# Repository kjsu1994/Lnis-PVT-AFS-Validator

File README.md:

# LNIS AFS End-to-End Validator

.NET 8 WPF에서 `LANS-AFS-SIM`과 `PocketSDR-AFS`를 별도 프로세스로 실행하여 AFS I/Q 생성, TCP 전송, 복호/PVT 처리 및 기준값 비교를 자동화한다.

## 1차 범위

```text
LANS-AFS-SIM -> INT8X2 I/Q -> TCP chunk/CRC32/SHA-256
             -> PocketSDR-AFS -> $LOG/$SB2/$POS -> 달 PVT 비교
```

실행에는 `LANS-AFS-SIM`과 `PocketSDR-AFS`만 사용한다. 범용 `PocketSDR`는 향후 GNSS 장비 Raw 입력과 지구 GNSS 기준 PVT Adapter를 구현할 때 참고한다. LNIS Codec, SF3/SF4 payload 삽입, BPv7/HDTN, SDR/RF와 실시간 스트리밍은 포함하지 않는다.

## 빌드

솔루션은 배포 가능한 WPF 본체 1개와 자동 테스트 프로젝트 1개로 구성된다. `Core`와 `Infrastructure`는 별도 프로젝트가 아닌 본체 내부 소스 폴더다.

```powershell
dotnet restore LnisAfsValidator.sln
dotnet build LnisAfsValidator.sln
dotnet test LnisAfsValidator.sln
dotnet run --project LnisAfsValidator.csproj
```

## WSL 준비

현재 확인 환경은 Ubuntu 24.04 WSL2이다. 애플리케이션은 패키지 설치나 저장소 복제를 자동 수행하지 않는다.

```bash
sudo apt update
sudo apt install build-essential git libusb-1.0-0-dev libfftw3-dev
cd /home/$USER
git clone https://github.com/osqzss/LANS-AFS-SIM.git
cd LANS-AFS-SIM && make

cd /home/$USER
git clone --recurse-submodules https://github.com/osqzss/PocketSDR-AFS.git
cd PocketSDR-AFS
git submodule update --init --recursive
cd lib/build && make && make install
cd ../../app/pocket_trk && make
```

기본 UI 경로는 `/home/imt` 기준 예시이므로 각 PC의 WSL 사용자 경로에 맞게 수정해야 한다. `O:` 드라이브 마운트에는 의존하지 않는다. WSL 산출물은 Windows의 `\\wsl.localhost\<배포판>\...` UNC를 통해 비동기로 읽고 쓴다.

## 사용 방법

공통으로 위치·시간 허용오차를 반드시 입력한다. `-b 2` 출력만 확인된 직접 호환 형식이므로 1차 UI는 `PocketSDR.INT8X2`, I/Q 2채널 형식을 고정 사용한다. 기준 시작 시각은 알마낙에서 결정된 생성기 stderr의 `Start time`을 사용한다.

### 로컬 시험

1. 역할을 `Local`로 선택한다.
2. 두 도구의 Native 또는 WSL 실행 경로와 작업 경로를 입력한다.
3. 월면 위치, 시험시간, 샘플률, 알마낙, PRN, 최소 위성 수와 허용오차를 입력한다.
4. `시험 시작`을 누른다. localhost에서도 실제 TCP 전송 경로를 사용한다.

### 두 PC 시험

1. 수신 PC에서 역할 `Receiver`, 사용할 포트와 PocketSDR-AFS 경로를 설정하고 먼저 시작한다.
2. OS 방화벽에서 해당 TCP 포트의 인바운드 연결을 허용한다.
3. 송신 PC에서 역할 `Sender`, 수신 PC 주소·동일 포트와 LANS-AFS-SIM 경로를 설정하고 시작한다.
4. 수신 PC는 무결성 ACK 후 복호/PVT를 수행하고 같은 연결로 최종 결과를 송신 PC에 반환한다.

## 판정과 결과

PASS에는 다음 근거가 모두 필요하다.

- 전송 byte count, chunk 순서, IEEE CRC32와 전체 SHA-256 일치
- 설정한 최소 위성 수 이상의 `SIGNAL FOUND`
- 최소 위성 수 이상의 `$SB2` 성공: AFS frame sync와 SB2 LDPC/CRC 성공의 간접 근거
- `$POS`와 마지막 필드의 실제 관측 위성 수
- 최종 `$POS` 위치·시간 오차가 사용자가 입력한 허용치 이내
- PocketSDR-AFS 정상 종료

명확한 필수 조건 위반은 Fail, 로그 형식 미지원이나 기준값 파싱 불가 등 근거 부족은 Inconclusive이다. `$POS`의 끝에서 두 번째 위성 수는 현재 AFS 소스에서 상수 `5`이므로 판정에 사용하지 않는다. `$SB3/$SB4`와 frame error는 기록하지만 1차 필수 조건은 아니다.

결과는 `%LOCALAPPDATA%\LnisAfsValidator\Runs` 아래에 manifest, JSON 결과, 생성기/수신기 원본 로그와 함께 저장한다. PASS면 대용량 I/Q를 삭제하고 Fail/Inconclusive이면 원본 분석을 위해 보관한다. 마지막 UI 설정은 `%LOCALAPPDATA%\LnisAfsValidator\settings.json`에 저장한다.

## TCP 프로토콜 v1

- magic/version: ASCII `LAFSIQ01`
- 최대 64 KiB 길이 제한 JSON manifest
- chunk: big-endian index, payload length, IEEE CRC32, payload
- 기본 chunk 1 MiB, 허용 범위 4 KiB~16 MiB, 기본 최대 파일 32 GiB
- 수신 경로는 원격 파일명을 사용하지 않고 시험 GUID로 생성
- SHA-256 확인 전에는 `.partial`, 성공 후에만 `.iq`로 원자적 변경

## 확장 지점

- `IIqDataSource`: 현재 LANS-AFS-SIM, 향후 GNSS 장비 Raw 및 PocketSDR 기준 PVT Adapter
- `IArtifactTransport`: 현재 TCP, 향후 BPv7/HDTN
- `IAfsReceiverAdapter`: 현재 PocketSDR-AFS, 향후 다른 AFS 수신기
- `IVerdictEvaluator`: 향후 LNIS message 및 SF3/SF4 비교

GNSS 장비 Raw 형식이 확인되기 전에는 이를 `Unknown` 산출물로 취급하고 성공으로 판정하지 않아야 한다. LNIS payload와 BPv7 bundle을 AFS SF3/SF4에 넣는 규격이 확인된 뒤 별도 Adapter로 구현한다.

## 현재 검증 제약

- .NET 솔루션 빌드와 자동 테스트는 수행 가능하다.
- 현재 PC의 WSL에는 필수 개발 패키지와 빌드된 오픈소스 실행 파일이 없어 실제 90초 AFS E2E는 아직 실행하지 못했다.
- 저장소에 AFS 실제 실행 로그 fixture가 없어 파서 테스트는 실제 소스에서 확인한 로그 형식을 사용한다. WSL 빌드 후 생성한 원본 로그로 fixture를 교체·보강해야 한다.
- `O:`가 WSL `/mnt/o`에 자동 마운트되지 않는 환경을 기준으로 UNC staging을 구현했다.

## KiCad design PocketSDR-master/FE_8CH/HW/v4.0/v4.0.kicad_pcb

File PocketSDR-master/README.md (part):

# **Pocket SDR - An Open-Source GNSS SDR,<br> ver. 0.19**

<div style="text-align: right;">
<strong>2026-07-24</strong>
</div>

---

## **Overview**

**Pocket SDR** is an open-source Global Navigation Satellite System (GNSS) receiver based
on software-defined radio (SDR) technology. It consists of RF frontend devices named
**Pocket SDR FE**, utilities for these devices, and GNSS SDR applications (APs) written
in Python, C, and C++. It supports almost all signals for **GPS**, **GLONASS**, **Galileo**,
**QZSS**, **BeiDou**, **NavIC**, and **SBAS**.

The Pocket SDR FE device includes 2, 4, or 8 RF frontend channels, supporting the
GNSS L1 band (1525 - 1610 MHz) or L2/L5/L6 bands (1160 - 1290 MHz). For these signal bands, refer to [**GNSS Signal Bands**](https://github.com/tomojitakasu/PocketSDR/blob/master/doc/signal_bands.pdf). Each RF channel
of the Pocket SDR FE device provides IF (intermediate-frequency) bandwidth of up to 36 MHz. The ADC sampling rate can be configured up to 32 Msps (FE 2CH) or 48 Msps (FE 4CH and FE 8CH).

Pocket SDR also includes utility programs to configure the Pocket SDR FE devices,
capture, and dump digitized IF data.
Additionally, Pocket SDR provides GNSS SDR APs to display the PSD (power spectrum density) of captured IF data, search for GNSS signals, track these signals, decode navigation data, and generate PVT (position, velocity, and time) solutions.
These utilities and APs are compatible with **Windows**, **Linux**, **Raspberry Pi OS**, **macOS**, and other environments.

The supported GNSS signals by Pocket SDR are as follows. For details on these signals and Pocket SDR signal IDs, refer to
[**GNSS Signals**](https://github.com/tomojitakasu/PocketSDR/blob/master/doc/signal_IDs.pdf).

* **GPS**: L1C/A, L1C-D, L1C-P, L2C-M, L5-I, L5-Q
* **GLONASS**: L1C/A (L1OF), L2C/A (L2OF), L1OCd, L1OCp, L2OCp, L3OCd, L3OCp
* **Galileo**: E1-B, E1-C, E5a-I, E5a-Q, E5b-I, E5b-Q, E5AltBOC (E5abQ), E6-B, E6-C
* **QZSS**: L1C/A, L1C/B, L1C-D, L1C-P, L1S, L2C-M, L5-I, L5-Q, L5S-I, L5S-Q, L6D, L6E
* **BeiDou**: B1I, B1C-D, B1C-P, B2a-D, B2a-P, B2I, B2b-I, B3I
* **NavIC**: L1-SPS-D, L1-SPS-P, L5-SPS
* **SBAS**: L1C/A, L5-I, L5-Q

These utilities and APs are written in Python, C, and C++ in a compact and modular way,
making them easy to modify for adding custom algorithms.

In addition to the Pocket SDR FE devices, Pocket SDR supports third-party
SDR hardware (**USRP**, **LimeSDR**, **bladRF**, **PlutoSDR**, **RTL-SDR**, and so on) via 
[**SoapySDR**](https://github.com/pothosware/SoapySDR/wiki).
See [**SoapySDR Device Notes**](https://github.com/tomojitakasu/PocketSDR/blob/master/doc/notes_soapy_dev.md) for verified devices,
installation notes, and device-specific caveats.

<p align="center">
  
  <b>Pocket SDR FE 2CH (v.2.0 and v.2.3), FE 4CH</b>
</p>

<p align="center">
  
  <b>Pocket SDR FE 8CH (2-RF-inputs and 8-RF-inputs)</b>
</p>

<p align="center">
  
  <b>GUI-based Real-Time GNSS SDR Receiver AP</b>
</p>

--------------------------------------------------------------------------------
<div class="pagebreak"></div>

## **Documents**

- Pocket SDR C Library API Reference
(https://github.com/tomojitakasu/PocketSDR/tree/master/doc/api_ref.pdf)

- Pocket SDR Command Reference
(https://github.com/tomojitakasu/PocketSDR/tree/master/doc/command_ref.pdf)

- Pocket SDR GNSS SDR Algorithm Description
(https://github.com/tomojitakasu/PocketSDR/tree/master/doc/algo_desc.pdf)

- Pocket SDR GNSS SDR アルゴリズム解説
(https://github.com/tomojitakasu/PocketSDR/tree/master/doc/algo_desc_jp.pdf)

- T.Takasu, An Open Source GNSS SDR: Development and Application, IPNTJ Next GNSS
Technology WG, February 21, 2022
(https://gpspp.sakura.ne.jp/paper2005/IPNTJ_NEXTWG_202202.pdf)

- T.Takasu, Development of QZSS L6 Receiver without Pilot Signal by using SDR,
IPNTJ Annual Conference, June 10, 2022
(https://gpspp.sakura.ne.jp/paper2005/IPNTJ_20220610.pdf)

- T.Takasu, Pocket SDR: Design, Implementation and Applications, A seminar for
GNSS Software Defined Receivers, Nov 19, 2024
(https://gpspp.sakura.ne.jp/paper2005/pocketsdr_seminar_202411_revA.pdf)

--------------------------------------------------------------------------------
<div class="pagebreak"></div>

## **Directory Structure and Contents**
```
PocketSDR
├── bin         # Pocket SDR APs binary programs
├── app         # Pocket SDR APs source programs
│   ├── pocket_conf  # Pocket SDR FE device configurator
│   ├── pocket_dump  # Dump digital IF data of Pocket SDR FE device
│   ├── pocket_scan  # Scan and list USB devices
│   ├── pocket_acq   # GNSS signal acquisition
│   ├── pocket_trk   # GNSS signal tracking and PVT generation
│   ├── pocket_snap  # Snapshot Positioning
│   ├── pocket_calib # Antenna array attitude / per-CH bias calibration
│   ├── convbin      # RINEX converter supporting Pocket SDR
│   └── str2str      # Stream converter (RTKLIB-derived)
├── src         # Pocket SDR library source programs
├── python      # Pocket SDR Python scripts (incl. pocket_sdr.py GUI)
├── lib         # Libraries for APs and Python scripts
│   ├── win32        # Built libraries for Windows (UCRT64)
│   ├── macos        # Built libraries for macOS
│   ├── linux        # Built libraries for Linux or Raspberry Pi OS
│   ├── build        # Makefiles to build libraries (UCRT64 / Linux / macOS)
│   ├── cyusb        # Cypress EZ-USB API (CyAPI.a) and includes
│   ├── RTKLIB       # RTKLIB source programs based on 2.4.3 b34
│   ├── pocketfft    # PocketFFT (header-only FFT, used internally)
│   └── SoapySDR     # SoapySDR headers + import lib for SDR device support
├── conf        # Configuration files for Pocket SDR FE
├── FE_2CH      # Pocket SDR FE 2CH H/W and F/W
├── FE_4CH      # Pocket SDR FE 4CH H/W and F/W
├── FE_8CH      # Pocket SDR FE 8CH H/W and F/W (3-bit RF samples)
├── driver      # Driver installation instruction for Pocket SDR FE
├── doc         # Documents (incl. api_ref.md, command_ref.md)
├── image       # Image files for documents
├── sample      # Sample digital IF data captured by Pocket SDR FE
└── test        # Test codes, scripts and data
    ├── python       # Python scripts for tests
    ├── script       # Shell scripts for tests
    ├── src          # source programs for tests
    └── utest        # makefile for unit tests

```
--------------------------------------------------------------------------------
<div class="pagebreak"></div>

## **Installation for Windows**

* Download and extract PocketSDR.zip or clone the git repository [**here**](https://github.com/tomojitakasu/PocketSDR) to an appropriate directory <install_dir>.
to an appropriate directory <install_dir>.
```
> unzip PocketSDR.zip
or
> git clone https://github.com/tomojitakasu/PocketSDR
```
* Install USB device driver for Pocket SDR FE according to [**driver/readme.txt**](https://github.com/tomojitakasu/PocketSDR/blob/master/driver/readme.txt)
.
* Install [**Python**](https://www.python.org/) with checking "Add python.exe to PATH".
* Install additional python packages as follows.
```
> pip install numpy scipy matplotlib
```
* (Optional) To use SoapySDR-supported devices (LimeSDR, HackRF, RTL-SDR,
  bladeRF, etc.), install [**radioconda**](https://github.com/ryanvolz/radioconda)
  and add `<radioconda_install_dir>\Library\bin` to PATH. See
  [SoapySDR Device Notes](https://github.com/tomojitakasu/PocketSDR/blob/master/doc/notes_soapy_dev.md#windows) for per-device
  packages, Zadig driver setup, and bladeRF version caveats.
* Add the Pocket SDR binary programs path (<install_dir>\PocketSDR\bin) to 
  the command search path (Path) of Windows environment variables.
* Add the Pocket SDR Python scripts path (<install_dir>\PocketSDR\python) to 
  the command search path (Path) of Windows environment variables.

--------------------------------------------------------------------------------

## **To rebuild binary programs for Windows**
* If you want to rebuild the binary utilities, APs, or shared libraries for the python APs
for Windows, you need [**MSYS2**](https://www.msys2.org/) with the **UCRT64** environment.
The UCRT64 toolchain links against the same C runtime (`ucrtbase.dll`) as
[**radioconda**](https://github.com/ryanvolz/radioconda)'s SoapySDR DLLs, which
gives stable high-rate streaming with SDR hardware (e.g., LimeSDR at 64 Msps).
The legacy **MINGW64** environment also builds, but suffers significant
performance loss with SoapySDR devices due to msvcrt/UCRT mixing.

* Open the **MSYS2 UCRT64** shell and install the development tools and the
  Python stack used by the python APs:
```
$ pacman -Syy
$ pacman -S git make
$ pacman -S mingw-w64-ucrt-x86_64-gcc
$ pacman -S mingw-w64-ucrt-x86_64-binutils
$ pacman -S mingw-w64-ucrt-x86_64-python
$ pacman -S mingw-w64-ucrt-x86_64-python-numpy
$ pacman -S mingw-w64-ucrt-x86_64-python-scipy
$ pacman -S mingw-w64-ucrt-x86_64-python-matplotlib
```
* If you intend to use SoapySDR-supported devices, install radioconda first.
  The default radioconda location used by the Makefiles is
  `/c/Users/<user>/radioconda/Library`. If installed elsewhere, override
  with `SOAPY_ROOT` on the make command line. See
  [SoapySDR Device Notes](https://github.com/tomojitakasu/PocketSDR/blob/master/doc/notes_soapy_dev.md#windows-build-notes)
  for details.

* If SoapySDR device support is not required, build `libsdr`, `pocket_trk`,
  and `pocket_dump` with `USE_SOAPY=0`. Pocket SDR FE USB devices and
  IF-file based processing still work; only SoapySDR device input is
  disabled. If you are rebuilding an existing tree, run `make clean` first.
```
$ cd <install_dir>/lib/build
$ make clean && make USE_SOAPY=0 && make install
$ cd <install_dir>/app/pocket_trk
$ make clean && make USE_SOAPY=0 && make install
$ cd <install_dir>/app/pocket_dump
$ make clean && make USE_SOAPY=0 && make install
```

* Move to the library build directory and build libraries.
```
$ cd <install_dir>/lib/build
$ make
$ make install
```
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
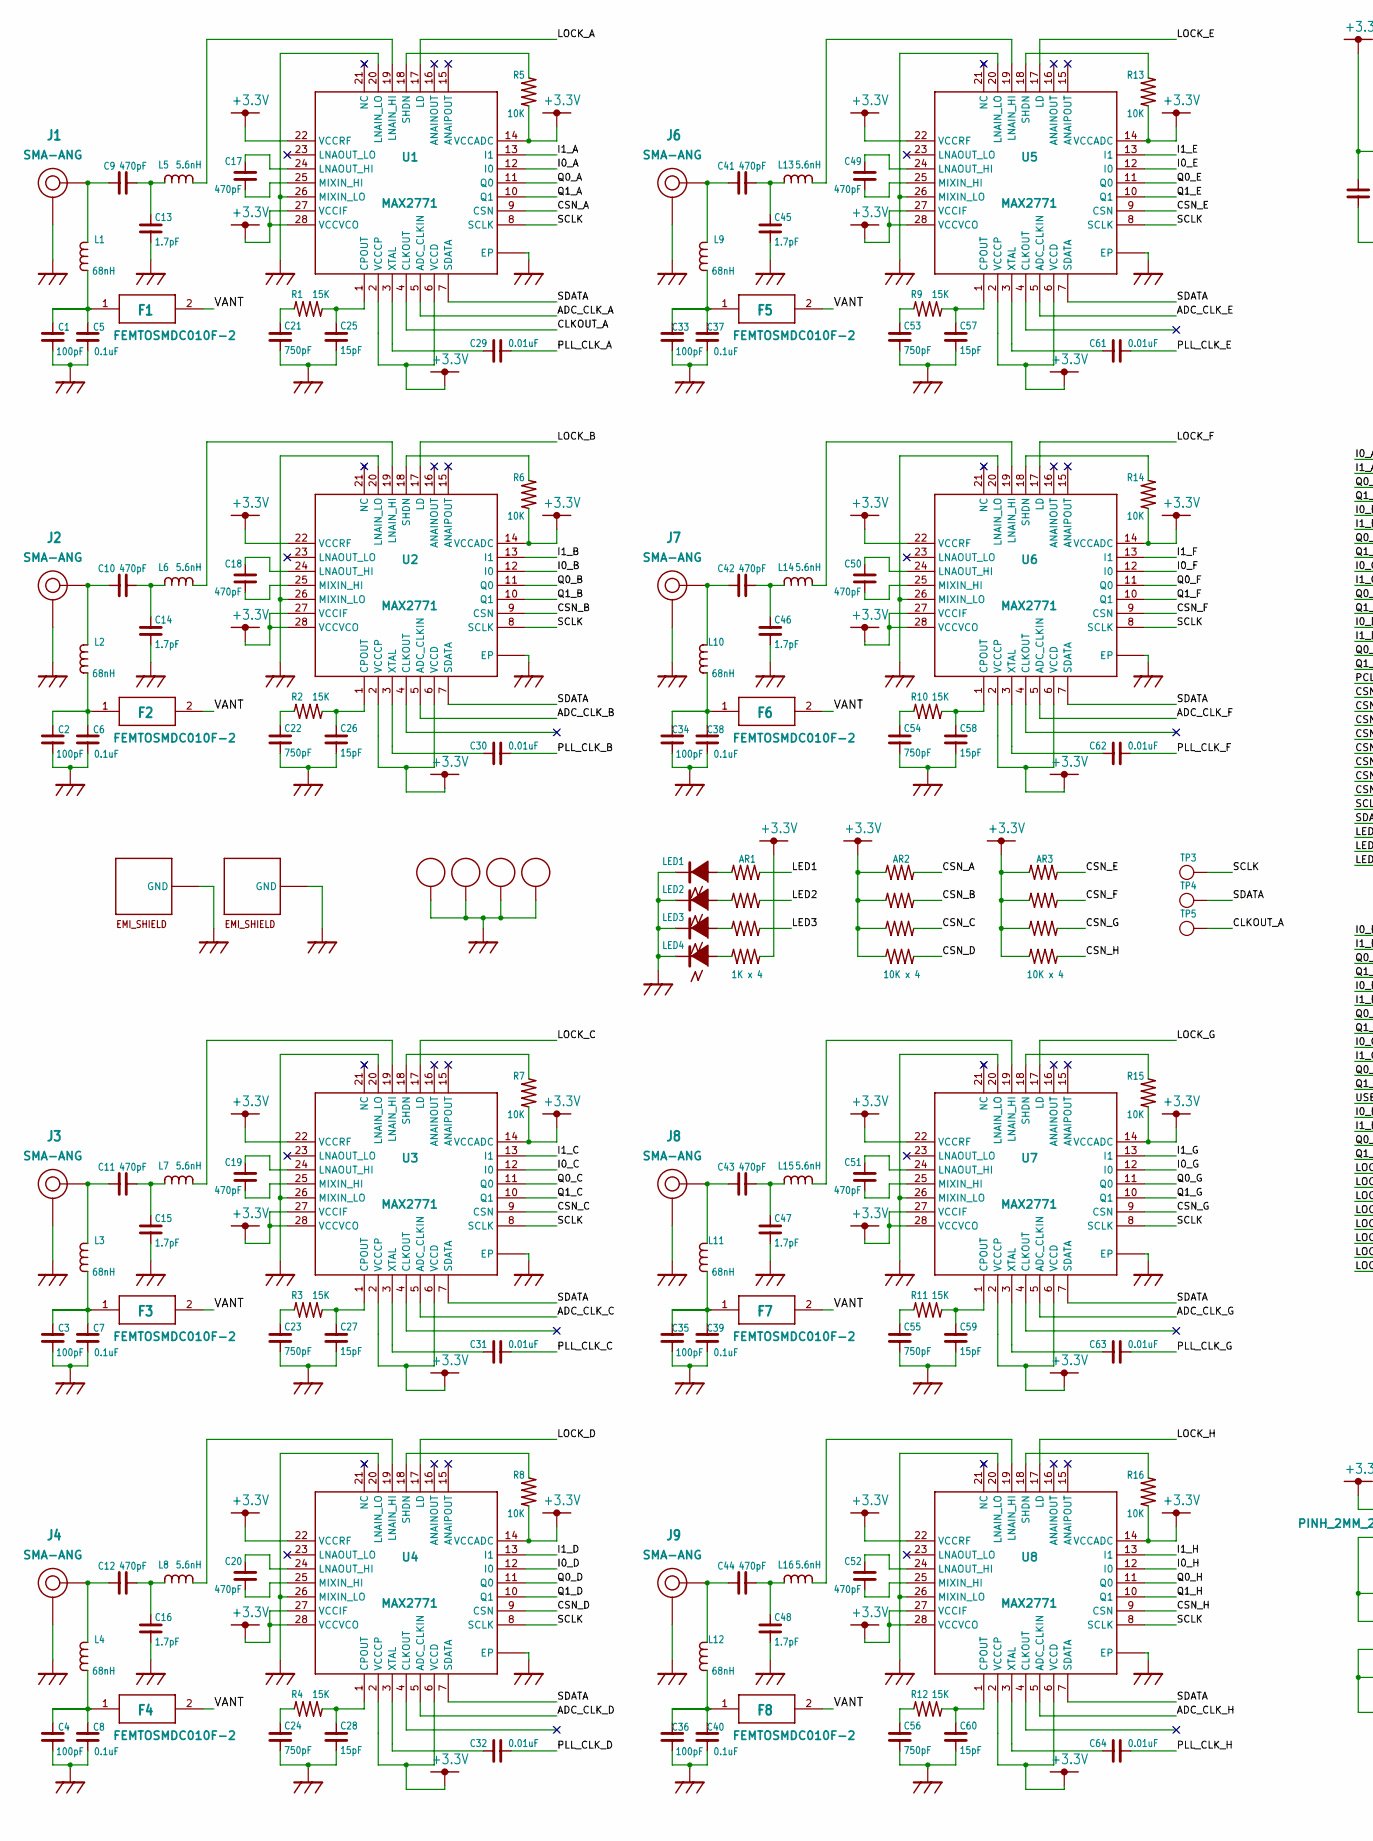
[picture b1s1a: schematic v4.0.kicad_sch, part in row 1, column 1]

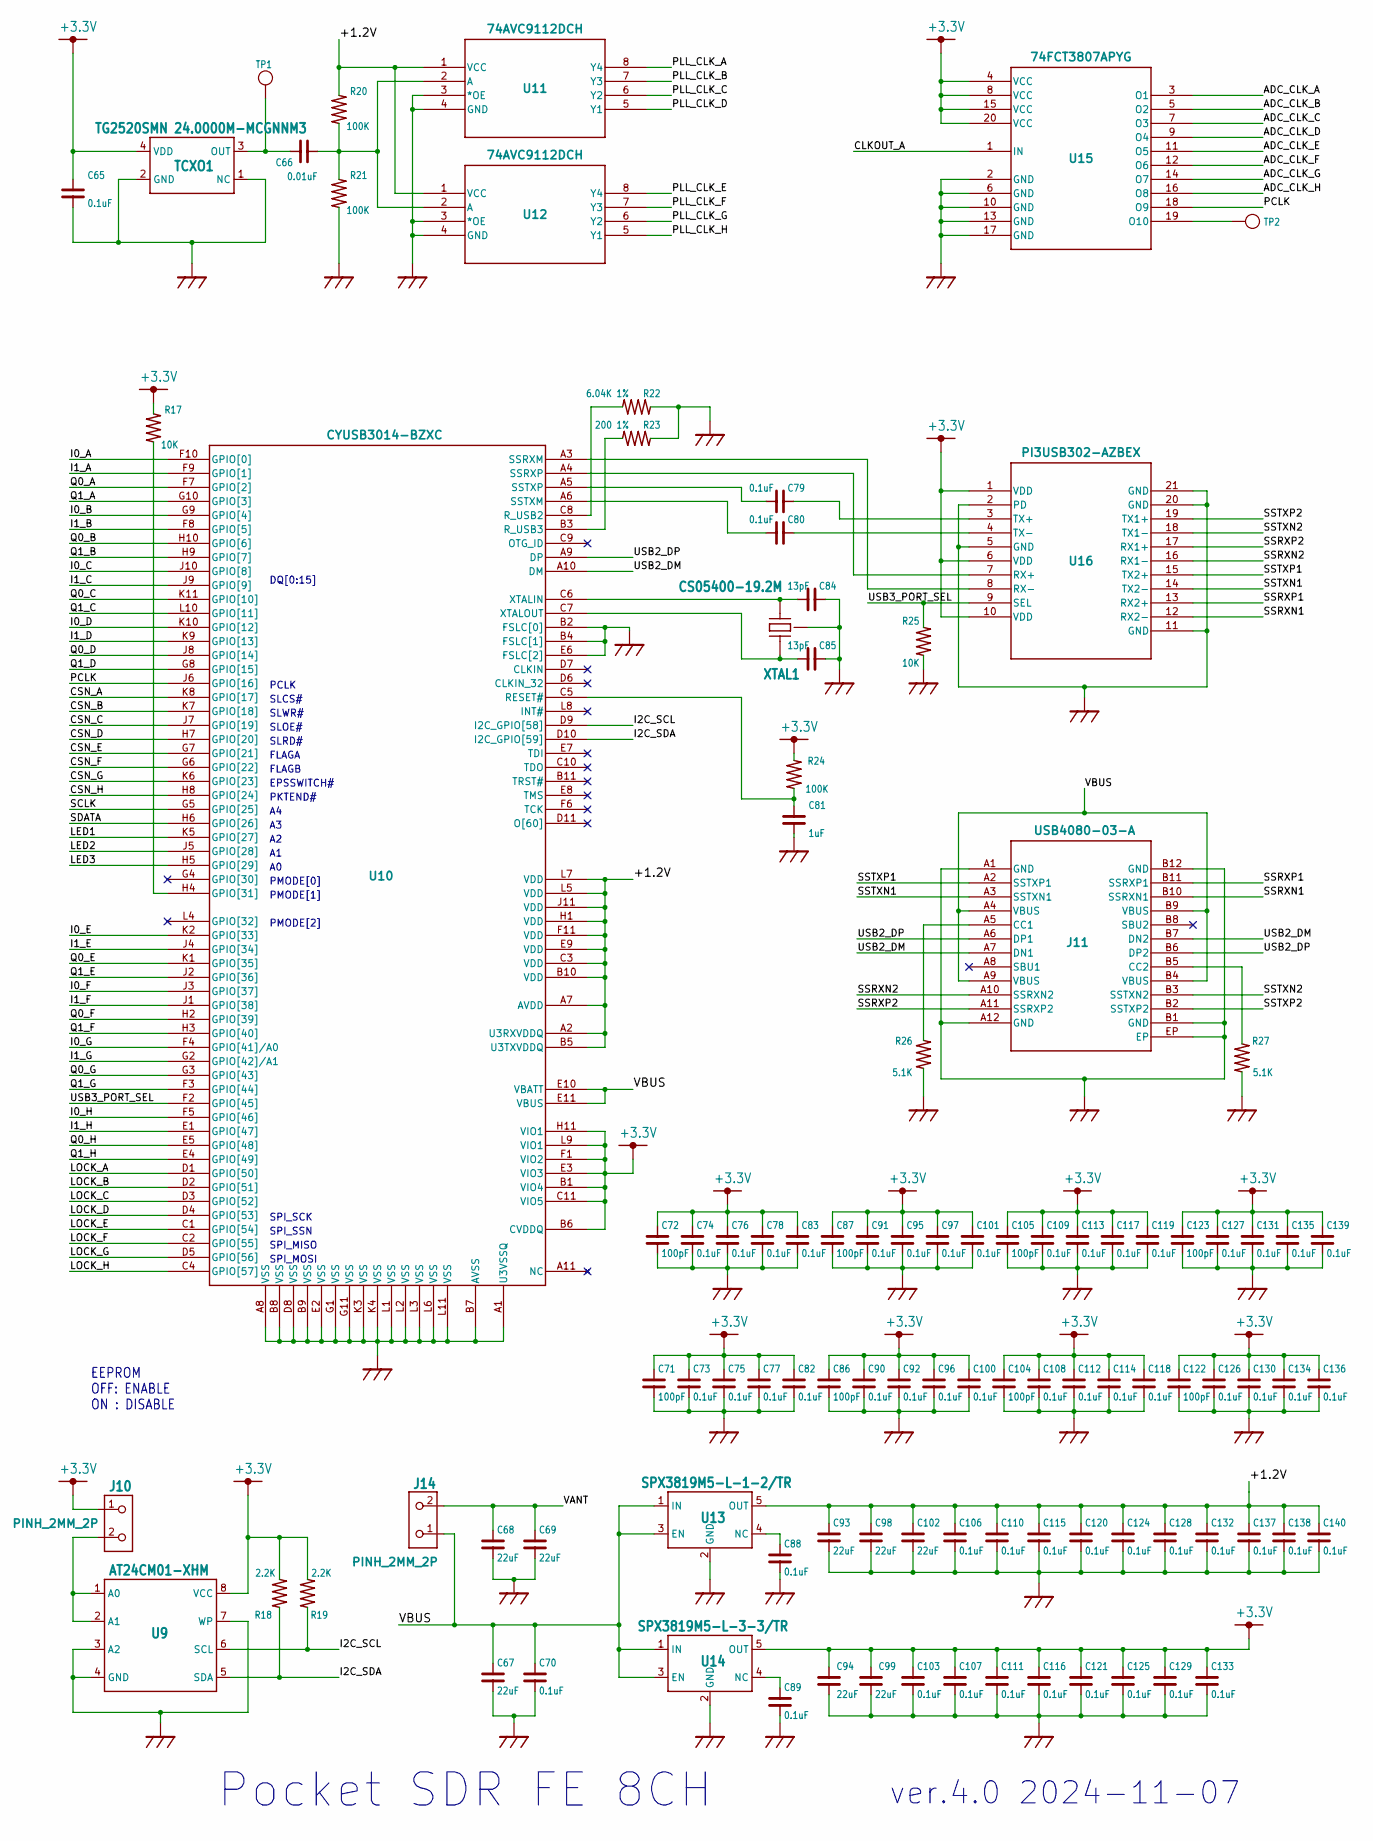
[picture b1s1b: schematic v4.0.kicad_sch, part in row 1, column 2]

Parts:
AR1: 1K x 4; EXB28V
AR2, AR3: 10K x 4; EXB28V
C1, C2, C3, C4, C33, C34, C35, C36, C71, C72, C86, C87, C104, C105, C122, C123: 100pF; C1005
C5, C6, C7, C8, C37, C38, C39, C40, C65, C70, C73, C74, C75, C76, C77, C78, C79, C80, C82, C83, C88, C89, C90, C91, C92, C95, C96, C97, C100, C101, C103, C106, C107, C108, C109, C110, C111, C112, C113, C114, C115, C116, C117, C118, C119, C120, C121, C124, C125, C126, C127, C128, C129, C130, C131, C132, C133, C134, C135, C136, C137, C138, C139, C140: 0.1uF; C1005
C9, C10, C11, C12, C17, C18, C19, C20, C41, C42, C43, C44, C49, C50, C51, C52: 470pF; C1005
C13, C14, C15, C16, C45, C46, C47, C48: 1.7pF; C1005
C21, C22, C23, C24, C53, C54, C55, C56: 750pF; C1005
C25, C26, C27, C28, C57, C58, C59, C60: 15pF; C1005
C29, C30, C31, C32, C61, C62, C63, C64, C66: 0.01uF; C1005
C67, C68, C69, C93, C94, C98, C99, C102: 22uF; C1608
C81: 1uF; C1005
C84, C85: 13pF; C1005
F1, F2, F3, F4, F5, F6, F7, F8: FEMTOSMDC010F-2; C1608
J1, J2, J3, J4, J6, J7, J8, J9: SMA-ANG
J10, J14: PINH_2MM_2P; PINH-2MM-2P
J11: USB4080-03-A; USB4080-03-A_GCT
J12, J13: MS448-10F
L1, L2, L3, L4, L9, L10, L11, L12: 68nH; C1608
L5, L6, L7, L8, L13, L14, L15, L16: 5.6nH; C1005
LED1, LED2, LED3, LED4: LED1608; LED_1608
PAD1, PAD2, PAD3, PAD4: CPAD_3.2MM
R1, R2, R3, R4, R9, R10, R11, R12: 15K; C1005
R5, R6, R7, R8, R13, R14, R15, R16, R17, R25: 10K; C1005
R18, R19: 2.2K; C1005
R20, R21, R24: 100K; C1005
R22: 6.04K 1%; C1005
R23: 200 1%; C1005
R26, R27: 5.1K; C1005
TCXO1: TG2520SMN 24.0000M-MCGNNM3; TCXO
TP1, TP2, TP3, TP4, TP5: TP0.5
U1, U2, U3, U4, U5, U6, U7, U8: MAX2771; TQFN28
U9: AT24CM01-XHM; TSSOP_8P
U10: CYUSB3014-BZXC; BGA-121
U11, U12: 74AVC9112DCH; VSSOP8_SOT765-1_NEX
U13: SPX3819M5-L-1-2/TR; SOT23
U14: SPX3819M5-L-3-3/TR; SOT23
U15: 74FCT3807APYG; SSOP20
U16: PI3USB302-AZBEX; 20TQFN-ZB_PI3USB302-A_DIO
XTAL1: CS05400-19.2M; XTAL_SMD

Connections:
+3.3V: AR1.8, AR2.1, AR2.3, AR2.5, AR2.7, AR3.1, AR3.3, AR3.5, AR3.7, C65.1, C71.1, C72.1, C73.1, C74.1, C75.1, C76.1, C77.1, C78.1, C82.1, C83.1, C86.1, C87.1, C90.1, C91.1, C92.1, C94.1, C95.1, C96.1, C97.1, C99.1, C100.1, C101.1, C103.1, C104.1, C105.1, C107.1, C108.1, C109.1, C111.1, C112.1, C113.1, C114.1, C116.1, C117.1, C118.1, C119.1, C121.1, C122.1, C123.1, C125.1, C126.1, C127.1, C129.1, C130.1, C131.1, C133.1, C134.1, C135.1, C136.1, C139.1, J10.1, R5.1, R6.1, R7.1, R8.1, R13.1, R14.1, R15.1, R16.1, R17.1, R18.2, R19.2, R24.2, TCXO1.4 (VDD), U1.2 (VCCCP), U1.6 (VCCD), U1.14 (VCCADC), U1.22 (VCCRF), U1.27 (VCCIF), U1.28 (VCCVCO), U2.2 (VCCCP), U2.6 (VCCD), U2.14 (VCCADC), U2.22 (VCCRF), U2.27 (VCCIF), U2.28 (VCCVCO), U3.2 (VCCCP), U3.6 (VCCD), U3.14 (VCCADC), U3.22 (VCCRF), U3.27 (VCCIF), U3.28 (VCCVCO), U4.2 (VCCCP), U4.6 (VCCD), U4.14 (VCCADC), U4.22 (VCCRF), U4.27 (VCCIF), U4.28 (VCCVCO), U5.2 (VCCCP), U5.6 (VCCD), U5.14 (VCCADC), U5.22 (VCCRF), U5.27 (VCCIF), U5.28 (VCCVCO), U6.2 (VCCCP), U6.6 (VCCD), U6.14 (VCCADC), U6.22 (VCCRF), U6.27 (VCCIF), U6.28 (VCCVCO), U7.2 (VCCCP), U7.6 (VCCD), U7.14 (VCCADC), U7.22 (VCCRF), U7.27 (VCCIF), U7.28 (VCCVCO), U8.2 (VCCCP), U8.6 (VCCD), U8.14 (VCCADC), U8.22 (VCCRF), U8.27 (VCCIF), U8.28 (VCCVCO), U9.8 (VCC), U10.B1 (VIO4), U10.B6 (CVDDQ), U10.C11 (VIO5), U10.E3 (VIO3), U10.F1 (VIO2), U10.H11 (VIO1), U10.L9 (VIO1), U14.5 (OUT), U15.4 (VCC), U15.8 (VCC), U15.15 (VCC), U15.20 (VCC), U16.1 (VDD), U16.6 (VDD), U16.10 (VDD)
/+1.2V: C93.1, C98.1, C102.1, C106.1, C110.1, C115.1, C120.1, C124.1, C128.1, C132.1, C137.1, C138.1, C140.1, R20.1, U10.A2 (U3RXVDDQ), U10.A7 (AVDD), U10.B5 (U3TXVDDQ), U10.B10 (VDD), U10.C3 (VDD), U10.E9 (VDD), U10.F11 (VDD), U10.H1 (VDD), U10.J11 (VDD), U10.L5 (VDD), U10.L7 (VDD), U11.1 (VCC), U12.1 (VCC), U13.5 (OUT)
/ADC_CLK_A: U1.5 (ADC_CLKIN), U15.3 (O1)
/ADC_CLK_B: U2.5 (ADC_CLKIN), U15.5 (O2)
/ADC_CLK_C: U3.5 (ADC_CLKIN), U15.7 (O3)
/ADC_CLK_D: U4.5 (ADC_CLKIN), U15.9 (O4)
/ADC_CLK_E: U5.5 (ADC_CLKIN), U15.11 (O5)
/ADC_CLK_F: U6.5 (ADC_CLKIN), U15.12 (O6)
/ADC_CLK_G: U7.5 (ADC_CLKIN), U15.14 (O7)
/ADC_CLK_H: U8.5 (ADC_CLKIN), U15.16 (O8)
/CLKOUT_A: TP5.1, U1.4 (CLKOUT), U15.1 (IN)
/CSN_A: AR2.2, U1.9 (CSN), U10.K8 (GPIO[17])
/CSN_B: AR2.4, U2.9 (CSN), U10.K7 (GPIO[18])
/CSN_C: AR2.6, U3.9 (CSN), U10.J7 (GPIO[19])
/CSN_D: AR2.8, U4.9 (CSN), U10.H7 (GPIO[20])
/CSN_E: AR3.2, U5.9 (CSN), U10.G7 (GPIO[21])
/CSN_F: AR3.4, U6.9 (CSN), U10.G6 (GPIO[22])
/CSN_G: AR3.6, U7.9 (CSN), U10.K6 (GPIO[23])
/CSN_H: AR3.8, U8.9 (CSN), U10.H8 (GPIO[24])
/I0_A: U1.12 (I0), U10.F10 (GPIO[0])
/I0_B: U2.12 (I0), U10.G9 (GPIO[4])
/I0_C: U3.12 (I0), U10.J10 (GPIO[8])
/I0_D: U4.12 (I0), U10.K10 (GPIO[12])
/I0_E: U5.12 (I0), U10.K2 (GPIO[33])
/I0_F: U6.12 (I0), U10.J3 (GPIO[37])
/I0_G: U7.12 (I0), U10.F4 (GPIO[41]/A0)
/I0_H: U8.12 (I0), U10.F5 (GPIO[46])
/I1_A: U1.13 (I1), U10.F9 (GPIO[1])
/I1_B: U2.13 (I1), U10.F8 (GPIO[5])
/I1_C: U3.13 (I1), U10.J9 (GPIO[9])
/I1_D: U4.13 (I1), U10.K9 (GPIO[13])
/I1_E: U5.13 (I1), U10.J4 (GPIO[34])
/I1_F: U6.13 (I1), U10.J1 (GPIO[38])
/I1_G: U7.13 (I1), U10.G2 (GPIO[42]/A1)
/I1_H: U8.13 (I1), U10.E1 (GPIO[47])
/I2C_SCL: R19.1, U9.6 (SCL), U10.D9 (I2C_GPIO[58])
/I2C_SDA: R18.1, U9.5 (SDA), U10.D10 (I2C_GPIO[59])
/LED1: AR1.2, U10.K5 (GPIO[27])
/LED2: AR1.4, U10.J5 (GPIO[28])
/LED3: AR1.6, U10.H5 (GPIO[29])
/LOCK_A: U1.17 (LD), U10.D1 (GPIO[50])
/LOCK_B: U2.17 (LD), U10.D2 (GPIO[51])
/LOCK_C: U3.17 (LD), U10.D3 (GPIO[52])
/LOCK_D: U4.17 (LD), U10.D4 (GPIO[53])
/LOCK_E: U5.17 (LD), U10.C1 (GPIO[54])
/LOCK_F: U6.17 (LD), U10.C2 (GPIO[55])
/LOCK_G: U7.17 (LD), U10.D5 (GPIO[56])
/LOCK_H: U8.17 (LD), U10.C4 (GPIO[57])
/PCLK: U10.J6 (GPIO[16]), U15.18 (O9)
/PLL_CLK_A: C29.1, U11.8 (Y4)
/PLL_CLK_B: C30.1, U11.7 (Y3)
/PLL_CLK_C: C31.1, U11.6 (Y2)
/PLL_CLK_D: C32.1, U11.5 (Y1)
/PLL_CLK_E: C61.1, U12.8 (Y4)
/PLL_CLK_F: C62.1, U12.7 (Y3)
/PLL_CLK_G: C63.1, U12.6 (Y2)
/PLL_CLK_H: C64.1, U12.5 (Y1)
/Q0_A: U1.11 (Q0), U10.F7 (GPIO[2])
/Q0_B: U2.11 (Q0), U10.H10 (GPIO[6])
/Q0_C: U3.11 (Q0), U10.K11 (GPIO[10])
/Q0_D: U4.11 (Q0), U10.J8 (GPIO[14])
/Q0_E: U5.11 (Q0), U10.K1 (GPIO[35])
/Q0_F: U6.11 (Q0), U10.H2 (GPIO[39])
/Q0_G: U7.11 (Q0), U10.G3 (GPIO[43])
/Q0_H: U8.11 (Q0), U10.E5 (GPIO[48])
/Q1_A: U1.10 (Q1), U10.G10 (GPIO[3])
/Q1_B: U2.10 (Q1), U10.H9 (GPIO[7])
/Q1_C: U3.10 (Q1), U10.L10 (GPIO[11])
/Q1_D: U4.10 (Q1), U10.G8 (GPIO[15])
/Q1_E: U5.10 (Q1), U10.J2 (GPIO[36])
/Q1_F: U6.10 (Q1), U10.H3 (GPIO[40])
/Q1_G: U7.10 (Q1), U10.F3 (GPIO[44])
/Q1_H: U8.10 (Q1), U10.E4 (GPIO[49])
/SCLK: TP3.1, U1.8 (SCLK), U2.8 (SCLK), U3.8 (SCLK), U4.8 (SCLK), U5.8 (SCLK), U6.8 (SCLK), U7.8 (SCLK), U8.8 (SCLK), U10.G5 (GPIO[25])
/SDATA: TP4.1, U1.7 (SDATA), U2.7 (SDATA), U3.7 (SDATA), U4.7 (SDATA), U5.7 (SDATA), U6.7 (SDATA), U7.7 (SDATA), U8.7 (SDATA), U10.H6 (GPIO[26])
/SSRXN1: J11.B10 (SSRXN1), U16.12 (RX2-)
/SSRXN2: J11.A10 (SSRXN2), U16.16 (RX1-)
/SSRXP1: J11.B11 (SSRXP1), U16.13 (RX2+)
/SSRXP2: J11.A11 (SSRXP2), U16.17 (RX1+)
/SSTXN1: J11.A3 (SSTXN1), U16.14 (TX2-)
/SSTXN2: J11.B3 (SSTXN2), U16.18 (TX1-)
/SSTXP1: J11.A2 (SSTXP1), U16.15 (TX2+)
/SSTXP2: J11.B2 (SSTXP2), U16.19 (TX1+)
/USB2_DM: J11.A7 (DN1), J11.B7 (DN2), U10.A10 (DM)
/USB2_DP: J11.A6 (DP1), J11.B6 (DP2), U10.A9 (DP)
/USB3_PORT_SEL: R25.2, U10.F2 (GPIO[45]), U16.9 (SEL)
/VANT: C68.1, C69.1, F1.2, F2.2, F3.2, F4.2, F5.2, F6.2, F7.2, F8.2, J14.2
/VBUS: C67.1, C70.1, J11.A4 (VBUS), J11.A9 (VBUS), J11.B4 (VBUS), J11.B9 (VBUS), J14.1, U10.E10 (VBATT), U10.E11 (VBUS), U13.1 (IN), U13.3 (EN), U14.1 (IN), U14.3 (EN)
GND: C1.1, C2.1, C3.1, C4.1, C5.1, C6.1, C7.1, C8.1, C13.1, C14.1, C15.1, C16.1, C21.2, C22.2, C23.2, C24.2, C25.2, C26.2, C27.2, C28.2, C33.1, C34.1, C35.1, C36.1, C37.1, C38.1, C39.1, C40.1, C45.1, C46.1, C47.1, C48.1, C53.2, C54.2, C55.2, C56.2, C57.2, C58.2, C59.2, C60.2, C65.2, C67.2, C68.2, C69.2, C70.2, C71.2, C72.2, C73.2, C74.2, C75.2, C76.2, C77.2, C78.2, C81.2, C82.2, C83.2, C84.1, C85.1, C86.2, C87.2, C88.2, C89.2, C90.2, C91.2, C92.2, C93.2, C94.2, C95.2, C96.2, C97.2, C98.2, C99.2, C100.2, C101.2, C102.2, C103.2, C104.2, C105.2, C106.2, C107.2, C108.2, C109.2, C110.2, C111.2, C112.2, C113.2, C114.2, C115.2, C116.2, C117.2, C118.2, C119.2, C120.2, C121.2, C122.2, C123.2, C124.2, C125.2, C126.2, C127.2, C128.2, C129.2, C130.2, C131.2, C132.2, C133.2, C134.2, C135.2, C136.2, C137.2, C138.2, C139.2, C140.2, J1.P2 (GND), J1.P3 (GND), J1.P4 (GND), J1.P5 (GND), J2.P2 (GND), J2.P3 (GND), J2.P4 (GND), J2.P5 (GND), J3.P2 (GND), J3.P3 (GND), J3.P4 (GND), J3.P5 (GND), J4.P2 (GND), J4.P3 (GND), J4.P4 (GND), J4.P5 (GND), J6.P2 (GND), J6.P3 (GND), J6.P4 (GND), J6.P5 (GND), J7.P2 (GND), J7.P3 (GND), J7.P4 (GND), J7.P5 (GND), J8.P2 (GND), J8.P3 (GND), J8.P4 (GND), J8.P5 (GND), J9.P2 (GND), J9.P3 (GND), J9.P4 (GND), J9.P5 (GND), J11.A1 (GND), J11.A12 (GND), J11.B1 (GND), J11.B12 (GND), J11.EP, J12.P (GND), J13.P (GND), LED1.2, LED2.2, LED3.2, LED4.2, PAD1.EP, PAD2.EP, PAD3.EP, PAD4.EP, R21.2, R22.1, R23.1, R25.1, R26.1, R27.1, TCXO1.1 (NC), TCXO1.2 (GND), U1.20 (LNAIN_LO), U1.26 (MIXIN_LO), U1.C1 (EP), U1.C2 (EP), U1.C3 (EP), U1.C4 (EP), U1.EP, U1.V1 (EP), U1.V2 (EP), U1.V3 (EP), U1.V4 (EP), U1.V5 (EP), U1.V6 (EP), U1.V7 (EP), U1.V8 (EP), U1.V9 (EP), U2.20 (LNAIN_LO), U2.26 (MIXIN_LO), U2.C1 (EP), U2.C2 (EP), U2.C3 (EP), U2.C4 (EP), U2.EP, U2.V1 (EP), U2.V2 (EP), U2.V3 (EP), U2.V4 (EP), U2.V5 (EP), U2.V6 (EP), U2.V7 (EP), U2.V8 (EP), U2.V9 (EP), U3.20 (LNAIN_LO), U3.26 (MIXIN_LO), U3.C1 (EP), U3.C2 (EP), U3.C3 (EP), U3.C4 (EP), U3.EP, U3.V1 (EP), U3.V2 (EP), U3.V3 (EP), U3.V4 (EP), U3.V5 (EP), U3.V6 (EP), U3.V7 (EP), U3.V8 (EP), U3.V9 (EP), U4.20 (LNAIN_LO), U4.26 (MIXIN_LO), U4.C1 (EP), U4.C2 (EP), U4.C3 (EP), U4.C4 (EP), U4.EP, U4.V1 (EP), U4.V2 (EP), U4.V3 (EP), U4.V4 (EP), U4.V5 (EP), U4.V6 (EP), U4.V7 (EP), U4.V8 (EP), U4.V9 (EP), U5.20 (LNAIN_LO), U5.26 (MIXIN_LO), U5.C1 (EP), U5.C2 (EP), U5.C3 (EP), U5.C4 (EP), U5.EP, U5.V1 (EP), U5.V2 (EP), U5.V3 (EP), U5.V4 (EP), U5.V5 (EP), U5.V6 (EP), U5.V7 (EP), U5.V8 (EP), U5.V9 (EP), U6.20 (LNAIN_LO), U6.26 (MIXIN_LO), U6.C1 (EP), U6.C2 (EP), U6.C3 (EP), U6.C4 (EP), U6.EP, U6.V1 (EP), U6.V2 (EP), U6.V3 (EP), U6.V4 (EP), U6.V5 (EP), U6.V6 (EP), U6.V7 (EP), U6.V8 (EP), U6.V9 (EP), U7.20 (LNAIN_LO), U7.26 (MIXIN_LO), U7.C1 (EP), U7.C2 (EP), U7.C3 (EP), U7.C4 (EP), U7.EP, U7.V1 (EP), U7.V2 (EP), U7.V3 (EP), U7.V4 (EP), U7.V5 (EP), U7.V6 (EP), U7.V7 (EP), U7.V8 (EP), U7.V9 (EP), U8.20 (LNAIN_LO), U8.26 (MIXIN_LO), U8.C1 (EP), U8.C2 (EP), U8.C3 (EP), U8.C4 (EP), U8.EP, U8.V1 (EP), U8.V2 (EP), U8.V3 (EP), U8.V4 (EP), U8.V5 (EP), U8.V6 (EP), U8.V7 (EP), U8.V8 (EP), U8.V9 (EP), U9.3 (A2), U9.4 (GND), U9.7 (WP), U10.A1 (U3VSSQ), U10.A8 (VSS), U10.B2 (FSLC[0]), U10.B4 (FSLC[1]), U10.B7 (AVSS), U10.B8 (VSS), U10.B9 (VSS), U10.D8 (VSS), U10.E2 (VSS), U10.E6 (FSLC[2]), U10.G1 (VSS), U10.G11 (VSS), U10.K3 (VSS), U10.K4 (VSS), U10.L1 (VSS), U10.L2 (VSS), U10.L3 (VSS), U10.L6 (VSS), U10.L11 (VSS), U11.3 (*OE), U11.4 (GND), U12.3 (*OE), U12.4 (GND), U13.2 (GND), U14.2 (GND), U15.2 (GND), U15.6 (GND), U15.10 (GND), U15.13 (GND), U15.17 (GND), U16.2 (PD), U16.5 (GND), U16.11 (GND), U16.20 (GND), U16.21 (GND), XTAL1.P2 (GND), XTAL1.P4 (GND)
unnamed: AR1.1, LED1.1 (+)
unnamed: AR1.3, LED2.1 (+)
unnamed: AR1.5, LED3.1 (+)
unnamed: AR1.7, LED4.1 (+)
unnamed: C1.2, C5.2, F1.1, L1.1
unnamed: C2.2, C6.2, F2.1, L2.1
unnamed: C3.2, C7.2, F3.1, L3.1
unnamed: C4.2, C8.2, F4.1, L4.1
unnamed: C33.2, C37.2, F5.1, L9.1
unnamed: C34.2, C38.2, F6.1, L10.1
unnamed: C35.2, C39.2, F7.1, L11.1
unnamed: C36.2, C40.2, F8.1, L12.1
unnamed: C9.1, J1.P1 (RF), L1.2
unnamed: C10.1, J2.P1 (RF), L2.2
unnamed: C11.1, J3.P1 (RF), L3.2
unnamed: C12.1, J4.P1 (RF), L4.2
unnamed: C41.1, J6.P1 (RF), L9.2
unnamed: C42.1, J7.P1 (RF), L10.2
unnamed: C43.1, J8.P1 (RF), L11.2
unnamed: C44.1, J9.P1 (RF), L12.2
unnamed: J10.2, U9.1 (A0), U9.2 (A1)
unnamed: J11.A5 (CC1), R26.2
unnamed: J11.B5 (CC2), R27.2
unnamed: C9.2, C13.2, L5.1
unnamed: L5.2, U1.19 (LNAIN_HI)
unnamed: C10.2, C14.2, L6.1
unnamed: L6.2, U2.19 (LNAIN_HI)
unnamed: C11.2, C15.2, L7.1
unnamed: L7.2, U3.19 (LNAIN_HI)
unnamed: C12.2, C16.2, L8.1
unnamed: L8.2, U4.19 (LNAIN_HI)
unnamed: C41.2, C45.2, L13.1
unnamed: L13.2, U5.19 (LNAIN_HI)
unnamed: C42.2, C46.2, L14.1
unnamed: L14.2, U6.19 (LNAIN_HI)
unnamed: C43.2, C47.2, L15.1
unnamed: L15.2, U7.19 (LNAIN_HI)
unnamed: C44.2, C48.2, L16.1
unnamed: L16.2, U8.19 (LNAIN_HI)
unnamed: C21.1, R1.1
unnamed: C25.1, R1.2, U1.1 (CPOUT)
unnamed: C22.1, R2.1
unnamed: C26.1, R2.2, U2.1 (CPOUT)
unnamed: C23.1, R3.1
unnamed: C27.1, R3.2, U3.1 (CPOUT)
unnamed: C24.1, R4.1
unnamed: C28.1, R4.2, U4.1 (CPOUT)
unnamed: R5.2, U1.18 (SHDN)
unnamed: R6.2, U2.18 (SHDN)
unnamed: R7.2, U3.18 (SHDN)
unnamed: R8.2, U4.18 (SHDN)
unnamed: C53.1, R9.1
unnamed: C57.1, R9.2, U5.1 (CPOUT)
unnamed: C54.1, R10.1
unnamed: C58.1, R10.2, U6.1 (CPOUT)
unnamed: C55.1, R11.1
unnamed: C59.1, R11.2, U7.1 (CPOUT)
unnamed: C56.1, R12.1
unnamed: C60.1, R12.2, U8.1 (CPOUT)
unnamed: R13.2, U5.18 (SHDN)
unnamed: R14.2, U6.18 (SHDN)
unnamed: R15.2, U7.18 (SHDN)
unnamed: R16.2, U8.18 (SHDN)
unnamed: R17.2, U10.H4 (GPIO[31])
unnamed: C66.2, R20.2, R21.1, U11.2 (A), U12.2 (A)
unnamed: R22.2, U10.C8 (R_USB2)
unnamed: R23.2, U10.B3 (R_USB3)
unnamed: C81.1, R24.1, U10.C5 (RESET#)
unnamed: C66.1, TCXO1.3 (OUT), TP1.1
unnamed: C17.1, U1.24 (LNAOUT_HI)
unnamed: C17.2, U1.25 (MIXIN_HI)
unnamed: C29.2, U1.3 (XTAL)
unnamed: C18.1, U2.24 (LNAOUT_HI)
unnamed: C18.2, U2.25 (MIXIN_HI)
unnamed: C30.2, U2.3 (XTAL)
unnamed: C19.1, U3.24 (LNAOUT_HI)
unnamed: C19.2, U3.25 (MIXIN_HI)
unnamed: C31.2, U3.3 (XTAL)
unnamed: C20.1, U4.24 (LNAOUT_HI)
unnamed: C20.2, U4.25 (MIXIN_HI)
unnamed: C32.2, U4.3 (XTAL)
unnamed: C49.1, U5.24 (LNAOUT_HI)
unnamed: C49.2, U5.25 (MIXIN_HI)
unnamed: C61.2, U5.3 (XTAL)
unnamed: C50.1, U6.24 (LNAOUT_HI)
unnamed: C50.2, U6.25 (MIXIN_HI)
unnamed: C62.2, U6.3 (XTAL)
unnamed: C51.1, U7.24 (LNAOUT_HI)
unnamed: C51.2, U7.25 (MIXIN_HI)
unnamed: C63.2, U7.3 (XTAL)
unnamed: C52.1, U8.24 (LNAOUT_HI)
unnamed: C52.2, U8.25 (MIXIN_HI)
unnamed: C64.2, U8.3 (XTAL)
unnamed: U10.A3 (SSRXM), U16.8 (RX-)
unnamed: U10.A4 (SSRXP), U16.7 (RX+)
unnamed: C80.2, U10.A6 (SSTXM)
unnamed: C79.2, U10.A5 (SSTXP)
unnamed: C84.2, U10.C6 (XTALIN), XTAL1.P1 (XTAL1)
unnamed: C85.2, U10.C7 (XTALOUT), XTAL1.P3 (XTAL2)
unnamed: C88.1, U13.4 (NC)
unnamed: C89.1, U14.4 (NC)
unnamed: TP2.1, U15.19 (O10)
unnamed: C79.1, U16.3 (TX+)
unnamed: C80.1, U16.4 (TX-)

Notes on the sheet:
PCLK
EPSSWITCH#
SPI_SSN
PMODE[1]
DQ[0:15]
Pocket SDR FE 8CH
PMODE[0]
EEPROM OFF: ENABLE ON : DISABLE
SPI_SCK
SPI_MOSI
SLRD#
SLOE#
SLCS#
PMODE[2]
SLWR#
PKTEND#
ver.4.0 2024-11-07
SPI_MISO
FLAGA
FLAGB

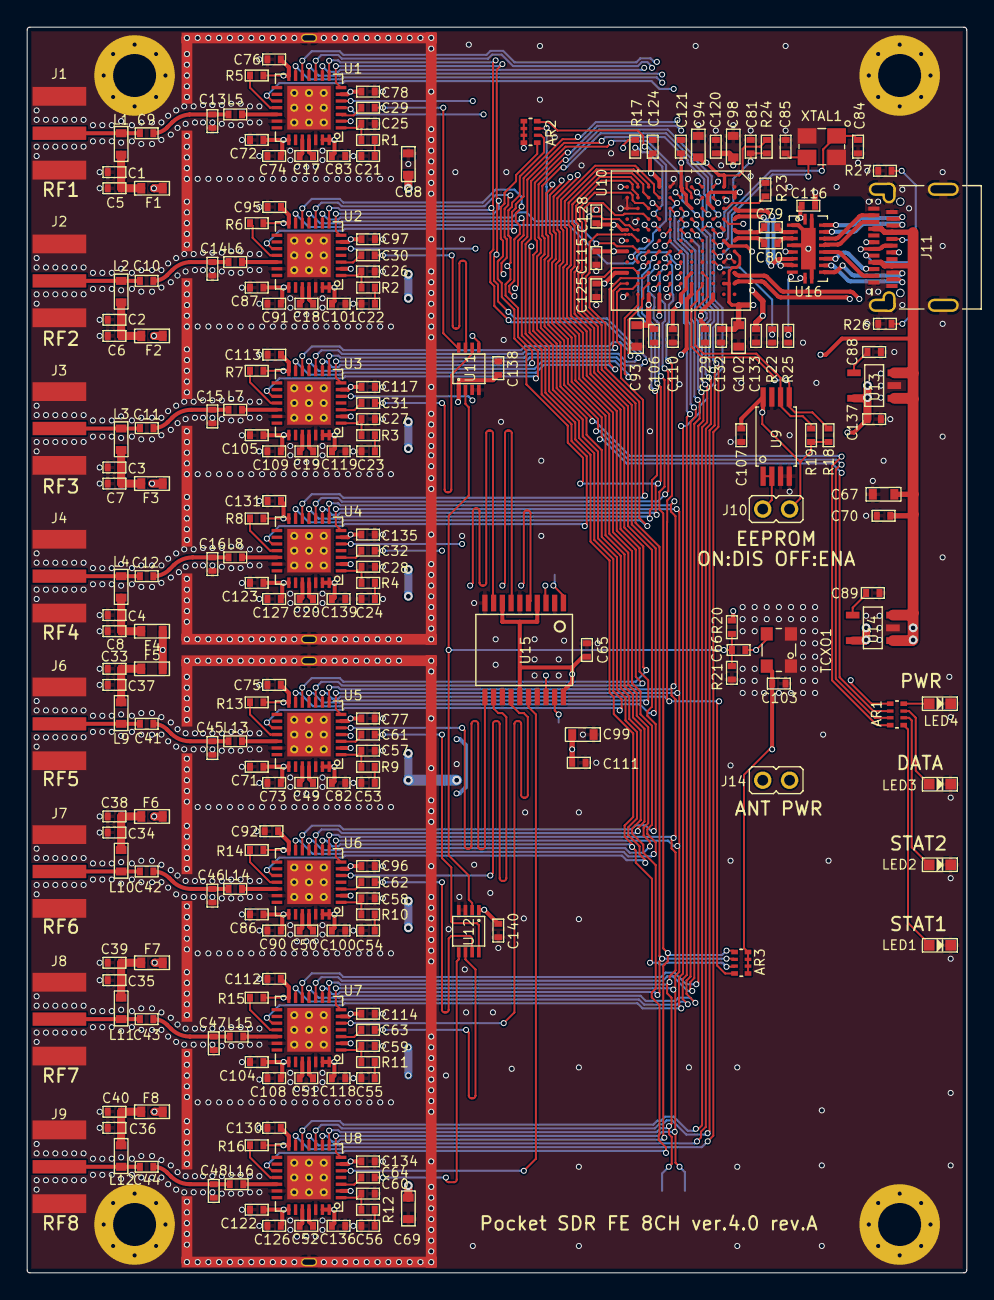
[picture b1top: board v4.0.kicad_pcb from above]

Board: 4 copper layers, 70.0 x 92.8 mm, 238 parts (0 on the bottom side), 193 nets.

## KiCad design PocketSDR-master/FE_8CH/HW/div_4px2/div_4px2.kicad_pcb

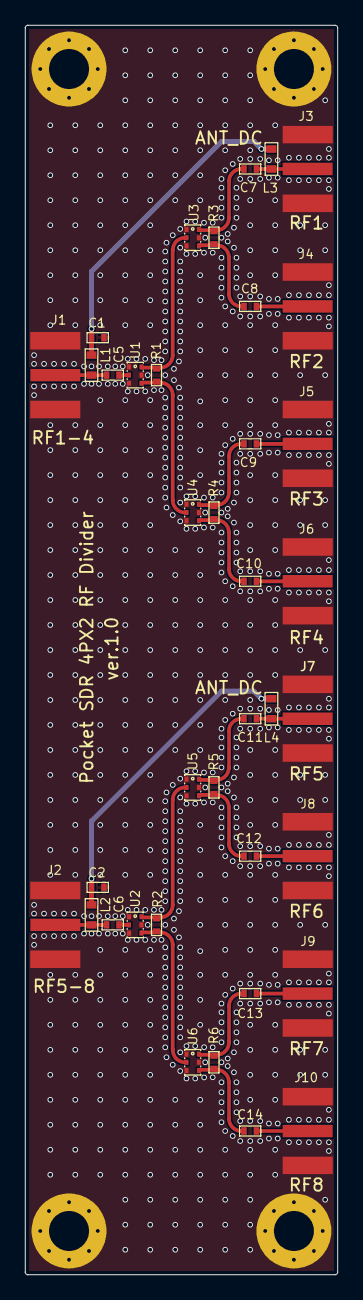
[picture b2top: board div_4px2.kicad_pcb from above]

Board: 4 copper layers, 25.0 x 100.0 mm, 42 parts (0 on the bottom side), 27 nets.

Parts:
C1, C2: 0.1uF; C1005
C5, C6, C7, C8, C9, C10, C11, C12, C13, C14: 100pF; C1005
J1, J2, J3, J4, J5, J6, J7, J8, J9, J10: SMA-ANG
L1, L2, L3, L4: 68nH; C1608
PAD1, PAD2, PAD3, PAD4: CPAD_3.2MM
R1, R2, R3, R4, R5, R6: 100; C1005
U1, U2, U3, U4, U5, U6: PD0922J5050S2HF; RF_DIV

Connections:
/ANT_DC1: C1.2, L1.1, L3.1
/ANT_DC2: C2.2, L2.1, L4.1
GND: C1.1, C2.1, J1.P2 (GND), J1.P3 (GND), J1.P4 (GND), J1.P5 (GND), J2.P2 (GND), J2.P3 (GND), J2.P4 (GND), J2.P5 (GND), J3.P2 (GND), J3.P3 (GND), J3.P4 (GND), J3.P5 (GND), J4.P2 (GND), J4.P3 (GND), J4.P4 (GND), J4.P5 (GND), J5.P2 (GND), J5.P3 (GND), J5.P4 (GND), J5.P5 (GND), J6.P2 (GND), J6.P3 (GND), J6.P4 (GND), J6.P5 (GND), J7.P2 (GND), J7.P3 (GND), J7.P4 (GND), J7.P5 (GND), J8.P2 (GND), J8.P3 (GND), J8.P4 (GND), J8.P5 (GND), J9.P2 (GND), J9.P3 (GND), J9.P4 (GND), J9.P5 (GND), J10.P2 (GND), J10.P3 (GND), J10.P4 (GND), J10.P5 (GND), PAD1.EP, PAD2.EP, PAD3.EP, PAD4.EP, U1.1 (GND@1), U1.3 (GND@2), U1.5 (GND@3), U2.1 (GND@1), U2.3 (GND@2), U2.5 (GND@3), U3.1 (GND@1), U3.3 (GND@2), U3.5 (GND@3), U4.1 (GND@1), U4.3 (GND@2), U4.5 (GND@3), U5.1 (GND@1), U5.3 (GND@2), U5.5 (GND@3), U6.1 (GND@1), U6.3 (GND@2), U6.5 (GND@3)
unnamed: C5.1, J1.P1 (RF), L1.2
unnamed: C6.1, J2.P1 (RF), L2.2
unnamed: C7.2, J3.P1 (RF), L3.2
unnamed: C8.2, J4.P1 (RF)
unnamed: C9.2, J5.P1 (RF)
unnamed: C10.2, J6.P1 (RF)
unnamed: C11.2, J7.P1 (RF), L4.2
unnamed: C12.2, J8.P1 (RF)
unnamed: C13.2, J9.P1 (RF)
unnamed: C14.2, J10.P1 (RF)
unnamed: R1.1, U1.4 (OUT1), U4.2 (INPUT)
unnamed: R1.2, U1.6 (OUT2), U3.2 (INPUT)
unnamed: R2.1, U2.4 (OUT1), U6.2 (INPUT)
unnamed: R2.2, U2.6 (OUT2), U5.2 (INPUT)
unnamed: C8.1, R3.1, U3.4 (OUT1)
unnamed: C7.1, R3.2, U3.6 (OUT2)
unnamed: C10.1, R4.1, U4.4 (OUT1)
unnamed: C9.1, R4.2, U4.6 (OUT2)
unnamed: C12.1, R5.1, U5.4 (OUT1)
unnamed: C11.1, R5.2, U5.6 (OUT2)
unnamed: C14.1, R6.1, U6.4 (OUT1)
unnamed: C13.1, R6.2, U6.6 (OUT2)
unnamed: C5.2, U1.2 (INPUT)
unnamed: C6.2, U2.2 (INPUT)

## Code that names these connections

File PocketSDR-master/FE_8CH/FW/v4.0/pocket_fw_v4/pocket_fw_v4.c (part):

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#ifndef F_TCXO
#define F_TCXO       24000      // TCXO frequency (kHz)
#endif
#define LOCK_A       50         // FX3 GPIO(50) <-- MAX2771 CH1 LD  (0x32)
#define LOCK_B       51         // FX3 GPIO(51) <-- MAX2771 CH2 LD  (0x33)
#define LOCK_C       52         // FX3 GPIO(52) <-- MAX2771 CH3 LD  (0x34)
#define LOCK_D       53         // FX3 GPIO(53) <-- MAX2771 CH4 LD  (0x35)
#define LOCK_E       54         // FX3 GPIO(54) <-- MAX2771 CH5 LD  (0x36)
#define LOCK_F       55         // FX3 GPIO(55) <-- MAX2771 CH6 LD  (0x37)
#define LOCK_G       56         // FX3 GPIO(56) <-- MAX2771 CH7 LD  (0x38)
#define LOCK_H       57         // FX3 GPIO(57) <-- MAX2771 CH8 LD  (0x39)
#define CSN_A        17         // FX3 GPIO(17) --> MAX2771 CH1 CSN (0x11)
#define CSN_B        18         // FX3 GPIO(18) --> MAX2771 CH2 CSN (0x12)
#define CSN_C        19         // FX3 GPIO(19) --> MAX2771 CH3 CSN (0x13)
#define CSN_D        20         // FX3 GPIO(20) --> MAX2771 CH4 CSN (0x14)
#define CSN_E        21         // FX3 GPIO(21) --> MAX2771 CH5 CSN (0x15)
#define CSN_F        22         // FX3 GPIO(22) --> MAX2771 CH6 CSN (0x16)
#define CSN_G        23         // FX3 GPIO(23) --> MAX2771 CH7 CSN (0x17)
#define CSN_H        24         // FX3 GPIO(24) --> MAX2771 CH8 CSN (0x18)
#define LED1         27         // FX3 GPIO(27) --> LED1            (0x1B)
#define LED2         28         // FX3 GPIO(28) --> LED2            (0x1C)
#define LED3         29         // FX3 GPIO(29) --> LED3            (0x1D)
#define USB3_PORT_SEL 45        // FX3 GPIO(45) --> USB3_PORT_SEL   (0x2D)
#define SCLK         25         // FX3 GPIO(25) --> MAX2771 SCLK    (0x19)
#define SDATA        26         // FX3 GPIO(26) <-> MAX2771 SDATA   (0x1A)
#define SCLK_CYC     10         // SPI SCLK delay

#define VR_STAT      0x40       // USB vendor request: Get device info and status
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static uint8_t EP0BUFF[128] __attribute__ ((aligned (32))); // EP0 data buffer

// IO ports definitions
static const uint8_t port_ena[] = {USB3_PORT_SEL, SCLK, CSN_E, CSN_F, CSN_G,
    CSN_H, LED1, LED2, LED3, LOCK_A, LOCK_B, LOCK_C, LOCK_D, LOCK_E, LOCK_F,
    LOCK_G, LOCK_H, SDATA, 0};
static const uint8_t port_out[] = {USB3_PORT_SEL, SCLK, CSN_A, CSN_B, CSN_C,
    CSN_D, CSN_E, CSN_F, CSN_G, CSN_H, LED1, LED2, LED3, 0};
static const uint8_t port_inp[] = {LOCK_A, LOCK_B, LOCK_C, LOCK_D, LOCK_E,
    LOCK_F, LOCK_G, LOCK_H, SDATA, 0};
static const uint8_t port_sdata[MAX_CH] = {SDATA, SDATA, SDATA, SDATA, SDATA,
    SDATA, SDATA, SDATA};
static const uint8_t port_csn[MAX_CH] = {CSN_A, CSN_B, CSN_C, CSN_D, CSN_E,
    CSN_F, CSN_G, CSN_H};

// default MAX2771 settings
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{
    // initialize P-port I/F block
    CyU3PPibClock_t pclk = {0};
    pclk.clkDiv = 2;
    pclk.clkSrc = CY_U3P_SYS_CLK;
    if (CyU3PPibInit(CyTrue, &pclk)) return 0;
    
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

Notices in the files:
PocketSDR-master/README.md:
h [**PocketFFT**](https://gitlab.mpcdf.mpg.de/mtr/pocketfft) (BSD-3-Clause) as the default FFT backend, replacing [**FFTW3**](https://www.fftw.org/) (GPL).
Note: FFTW3 is GPL-licensed, so a binary linked against it inherits GPL terms. Keep this in mind when redistributing.
